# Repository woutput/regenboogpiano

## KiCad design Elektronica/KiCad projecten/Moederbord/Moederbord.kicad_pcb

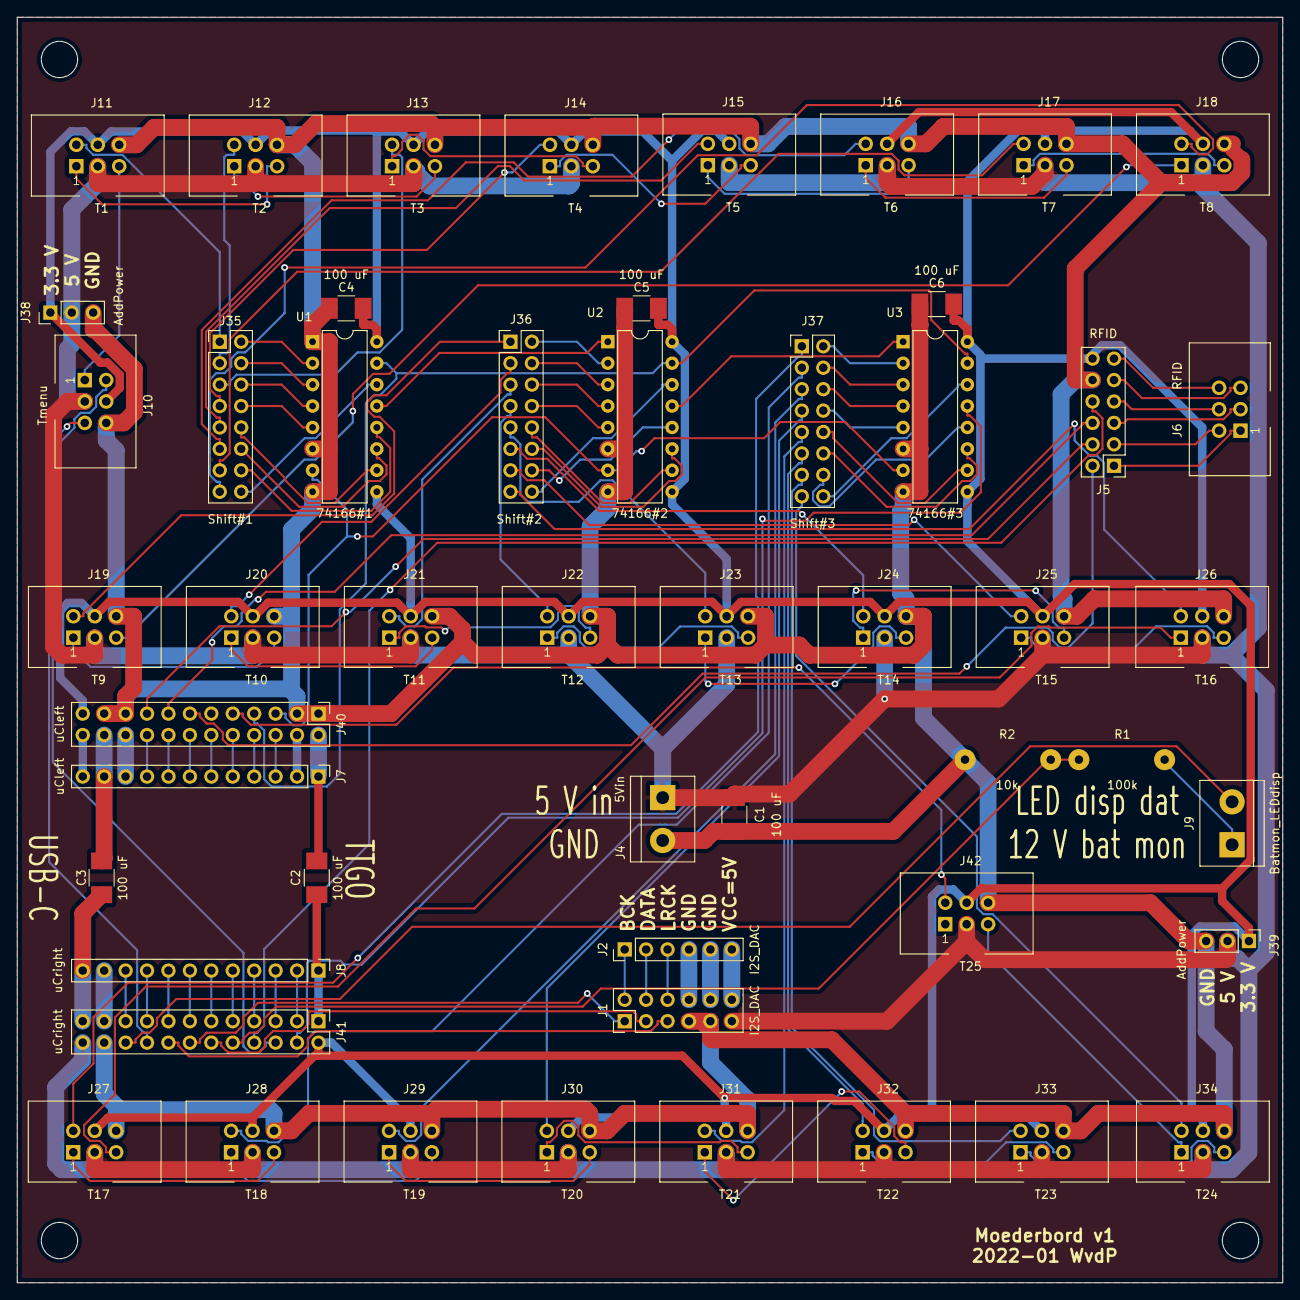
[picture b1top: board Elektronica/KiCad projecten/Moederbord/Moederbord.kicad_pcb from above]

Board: 2 copper layers, 150.0 x 150.0 mm, 56 parts (0 on the bottom side), 130 nets.

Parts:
C1, C2, C3, C4, C5, C6: 100 uF; C_1210_HandSoldering
J1: I2S_DAC; Pin_Header_Straight_2x06_Pitch2.54mm
J2: I2S_DAC; Socket_Strip_Straight_1x06_Pitch2.54mm
J4: 5Vin; TerminalBlock_2_P5.08mm
J5: RFID; Pin_Header_Straight_2x06_Pitch2.54mm
J6: RFID; IDC_Header_Straight_6pins
J7: uCleft; Socket_Strip_Straight_1x12_Pitch2.54mm
J8: uCright; Socket_Strip_Straight_1x12_Pitch2.54mm
J9: Batmon_LEDdisp; TerminalBlock_2_P5.08mm
J10: Tmenu; IDC_Header_Straight_6pins
J11: T1; IDC_Header_Straight_6pins
J12: T2; IDC_Header_Straight_6pins
J13: T3; IDC_Header_Straight_6pins
J14: T4; IDC_Header_Straight_6pins
J15: T5; IDC_Header_Straight_6pins
J16: T6; IDC_Header_Straight_6pins
J17: T7; IDC_Header_Straight_6pins
J18: T8; IDC_Header_Straight_6pins
J19: T9; IDC_Header_Straight_6pins
J20: T10; IDC_Header_Straight_6pins
J21: T11; IDC_Header_Straight_6pins
J22: T12; IDC_Header_Straight_6pins
J23: T13; IDC_Header_Straight_6pins
J24: T14; IDC_Header_Straight_6pins
J25: T15; IDC_Header_Straight_6pins
J26: T16; IDC_Header_Straight_6pins
J27: T17; IDC_Header_Straight_6pins
J28: T18; IDC_Header_Straight_6pins
J29: T19; IDC_Header_Straight_6pins
J30: T20; IDC_Header_Straight_6pins
J31: T21; IDC_Header_Straight_6pins
J32: T22; IDC_Header_Straight_6pins
J33: T23; IDC_Header_Straight_6pins
J34: T24; IDC_Header_Straight_6pins
J35: Shift#1; Pin_Header_Straight_2x08_Pitch2.54mm
J36: Shift#2; Pin_Header_Straight_2x08_Pitch2.54mm
J37: Shift#3; Pin_Header_Straight_2x08_Pitch2.54mm
J38, J39: AddPower; Pin_Header_Straight_1x03_Pitch2.54mm
J40: uCleft; Pin_Header_Straight_2x12_Pitch2.54mm
J41: uCright; Pin_Header_Straight_2x12_Pitch2.54mm
J42: T25; IDC_Header_Straight_6pins
R1: 100k; WireConnection_1.00mmDrill
R2: 10k; WireConnection_1.00mmDrill
U1: 74166#1; DIP-16_W7.62mm
U2: 74166#2; DIP-16_W7.62mm
U3: 74166#3; DIP-16_W7.62mm
X1, X2, X3, X4: MountingHole_4.3mm_M4

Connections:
+3V3: C4.1, C5.1, C6.1, J5.12, J10.4, J11.4, J12.4, J13.4, J14.4, J15.4, J16.4, J17.4, J18.4, J19.4, J20.4, J21.4, J22.4, J23.4, J24.4, J25.4, J26.4, J27.4, J28.4, J29.4, J30.4, J31.4, J32.4, J33.4, J34.4, J38.1, J39.1, J40.23, J41.2, J42.4, U1.9, U1.16, U2.9, U2.16, U3.9, U3.16
+5V: C1.2, J1.11, J4.1, J10.3, J11.3, J12.3, J13.3, J14.3, J15.3, J16.3, J17.3, J18.3, J19.3, J20.3, J21.3, J22.3, J23.3, J24.3, J25.3, J26.3, J27.3, J28.3, J29.3, J30.3, J31.3, J32.3, J33.3, J34.3, J38.2, J39.2, J41.24, J42.3
/Shift registers/T1: J35.2, U1.2
/Shift registers/T2: J35.4, U1.3
/Shift registers/T3: J35.6, U1.4
/Shift registers/T4: J35.8, U1.5
/Shift registers/T5: J35.10, U1.10
/Shift registers/T6: J35.12, U1.11
/Shift registers/T7: J35.14, U1.12
/Shift registers/T8: J35.16, U1.14
/Shift registers/T9: J36.2, U2.2
/Shift registers/T10: J36.4, U2.3
/Shift registers/T11: J36.6, U2.4
/Shift registers/T12: J36.8, U2.5
/Shift registers/T13: J36.10, U2.10
/Shift registers/T14: J36.12, U2.11
/Shift registers/T15: J36.14, U2.12
/Shift registers/T16: J36.16, U2.14
/Shift registers/T17: J37.2, U3.2
/Shift registers/T18: J37.4, U3.3
/Shift registers/T19: J37.6, U3.4
/Shift registers/T20: J37.8, U3.5
/Shift registers/T21: J37.10, U3.10
/Shift registers/T22: J37.12, U3.11
/Shift registers/T23: J37.14, U3.12
/Shift registers/T24: J37.16, U3.14
/Shift registers/s1_s2: U1.13, U2.1
/Shift registers/s2_s3: U2.13, U3.1
/Toetsmodules/LED1_LED2: J11.1, J12.5
/Toetsmodules/LED2_LED3: J12.1, J13.5
/Toetsmodules/LED3_LED4: J13.1, J14.5
/Toetsmodules/LED4_LED5: J14.1, J15.5
/Toetsmodules/LED5_LED6: J15.1, J16.5
/Toetsmodules/LED6_LED7: J16.1, J17.5
/Toetsmodules/LED7_LED8: J17.1, J18.5
/Toetsmodules/LED8_LED9: J18.1, J19.5
/Toetsmodules/LED9_LED10: J19.1, J20.5
/Toetsmodules/LED10_LED11: J20.1, J21.5
/Toetsmodules/LED11_LED12: J21.1, J22.5
/Toetsmodules/LED12_LED13: J22.1, J23.5
/Toetsmodules/LED13_LED14: J23.1, J24.5
/Toetsmodules/LED14_LED15: J24.1, J25.5
/Toetsmodules/LED15_LED16: J25.1, J26.5
/Toetsmodules/LED16_LED17: J26.1, J27.5
/Toetsmodules/LED17_LED18: J27.1, J28.5
/Toetsmodules/LED18_LED19: J28.1, J29.5
/Toetsmodules/LED19_LED20: J29.1, J30.5
/Toetsmodules/LED20_LED21: J30.1, J31.5
/Toetsmodules/LED21_LED22: J31.1, J32.5
/Toetsmodules/LED22_LED23: J32.1, J33.5
/Toetsmodules/LED23_LED24: J33.1, J34.5
/Toetsmodules/LED24_LED25: J34.1, J42.5
/Toetsmodules/LEDm_LED1: J10.1, J11.5
/Vbat12V: J9.1, R1.1
BatMon: J41.10, R1.2, R2.1
DAC_BCK: J1.1, J41.14
DAC_DATA: J1.3, J41.12
DAC_LRCK: J1.5, J41.16
GND: C1.1, C4.2, C5.2, C6.2, J1.7, J1.9, J4.2, J5.10, J10.6, J11.6, J12.6, J13.6, J14.6, J15.6, J16.6, J17.6, J18.6, J19.6, J20.6, J21.6, J22.6, J23.6, J24.6, J25.6, J26.6, J27.6, J28.6, J29.6, J30.6, J31.6, J32.6, J33.6, J34.6, J38.3, J39.3, J40.1, J40.3, J40.19, J40.21, J41.22, J42.6, R2.2, U1.1, U1.6, U1.8, U2.6, U2.8, U3.6, U3.8
LED_display_data: J9.2, J41.20
LED_rings_data: J10.5, J41.18
unnamed: C2.1, J8.1, J41.1
unnamed: C2.2, J7.1, J40.2
unnamed: C3.1, J8.12, J41.23
unnamed: C3.2, J7.11, J40.22
unnamed: J1.2, J2.1
unnamed: J1.4, J2.2
unnamed: J1.6, J2.3
unnamed: J1.8, J2.4
unnamed: J1.10, J2.5
unnamed: J1.12, J2.6
unnamed: J5.1, J6.1
unnamed: J5.3, J6.2
unnamed: J5.5, J6.3
unnamed: J5.7, J6.4
unnamed: J5.9, J6.5
unnamed: J5.11, J6.6
unnamed: J7.2, J40.4
unnamed: J7.3, J40.6
unnamed: J7.4, J40.8
unnamed: J7.5, J40.10
unnamed: J7.6, J40.12
unnamed: J7.7, J40.14
unnamed: J7.8, J40.16
unnamed: J7.9, J40.18
unnamed: J7.10, J40.20
unnamed: J7.12, J40.24
unnamed: J8.2, J41.3
unnamed: J8.3, J41.5
unnamed: J8.4, J41.7
unnamed: J8.5, J41.9
unnamed: J8.6, J41.11
unnamed: J8.7, J41.13
unnamed: J8.8, J41.15
unnamed: J8.9, J41.17
unnamed: J8.10, J41.19
unnamed: J8.11, J41.21
RFID_CS: J5.2, J40.13
RFID_MISO: J5.8, J41.8
RFID_MOSI: J5.6, J40.15
RFID_SCLK: J5.4, J40.17
Shift_CLK: J40.5, U1.7, U2.7, U3.7
Shift_SH_LDn: J40.7, U1.15, U2.15, U3.15
Shift_data: J41.4, U3.13
Touch1: J11.2, J35.1
Touch2: J12.2, J35.3
Touch3: J13.2, J35.5
Touch4: J14.2, J35.7
Touch5: J15.2, J35.9
Touch6: J16.2, J35.11
Touch7: J17.2, J35.13
Touch8: J18.2, J35.15
Touch9: J19.2, J36.1
Touch10: J20.2, J36.3
Touch11: J21.2, J36.5
Touch12: J22.2, J36.7
Touch13: J23.2, J36.9
Touch14: J24.2, J36.11
Touch15: J25.2, J36.13
Touch16: J26.2, J36.15
Touch17: J27.2, J37.1
Touch18: J28.2, J37.3
Touch19: J29.2, J37.5
Touch20: J30.2, J37.7
Touch21: J31.2, J37.9
Touch22: J32.2, J37.11
Touch23: J33.2, J37.13
Touch24: J34.2, J37.15
Touch25: J40.9, J42.2
Touch_menu: J10.2, J41.6

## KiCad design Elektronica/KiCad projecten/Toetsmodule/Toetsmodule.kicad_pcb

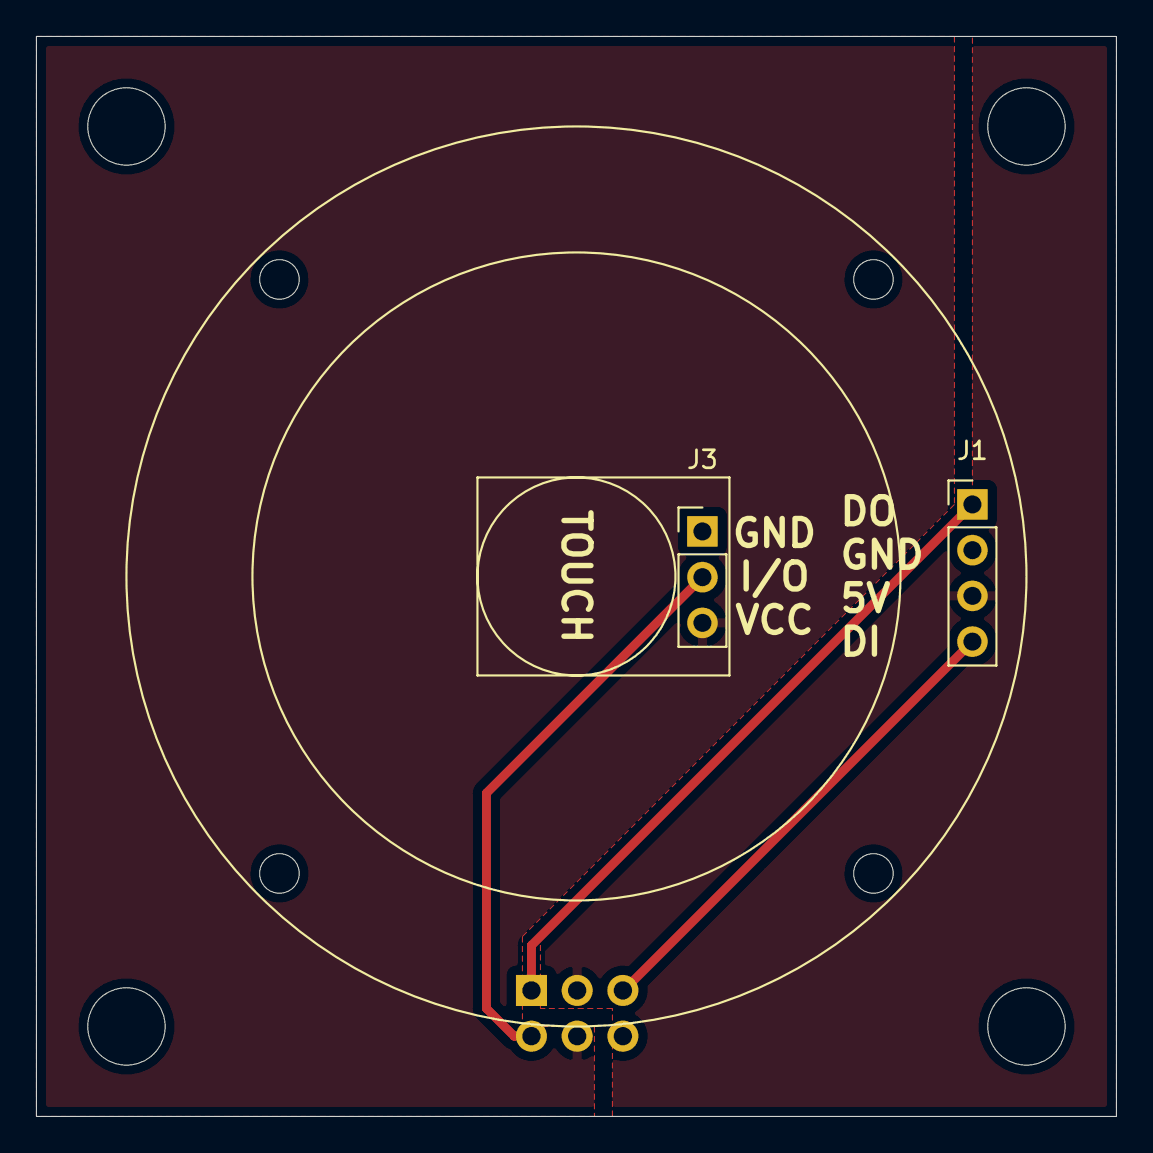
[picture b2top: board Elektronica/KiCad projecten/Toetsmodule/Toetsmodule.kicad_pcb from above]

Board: 2 copper layers, 60.0 x 60.0 mm, 3 parts (1 on the bottom side), 6 nets.

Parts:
J1: Conn_01x04_Male; Pin_Header_Straight_1x04_Pitch2.54mm
J2: Conn_01x06_Male; IDC_Header_Straight_6pins
J3: Touch module; Pin_Header_Straight_1x03_Pitch2.54mm

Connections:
+3V3: J2.4, J3.3
+5V: J1.3, J2.3
/LED_in: J1.4, J2.5
/LED_out: J1.1, J2.1
/Touch_output: J2.2, J3.2
GND: J1.2, J2.6, J3.1

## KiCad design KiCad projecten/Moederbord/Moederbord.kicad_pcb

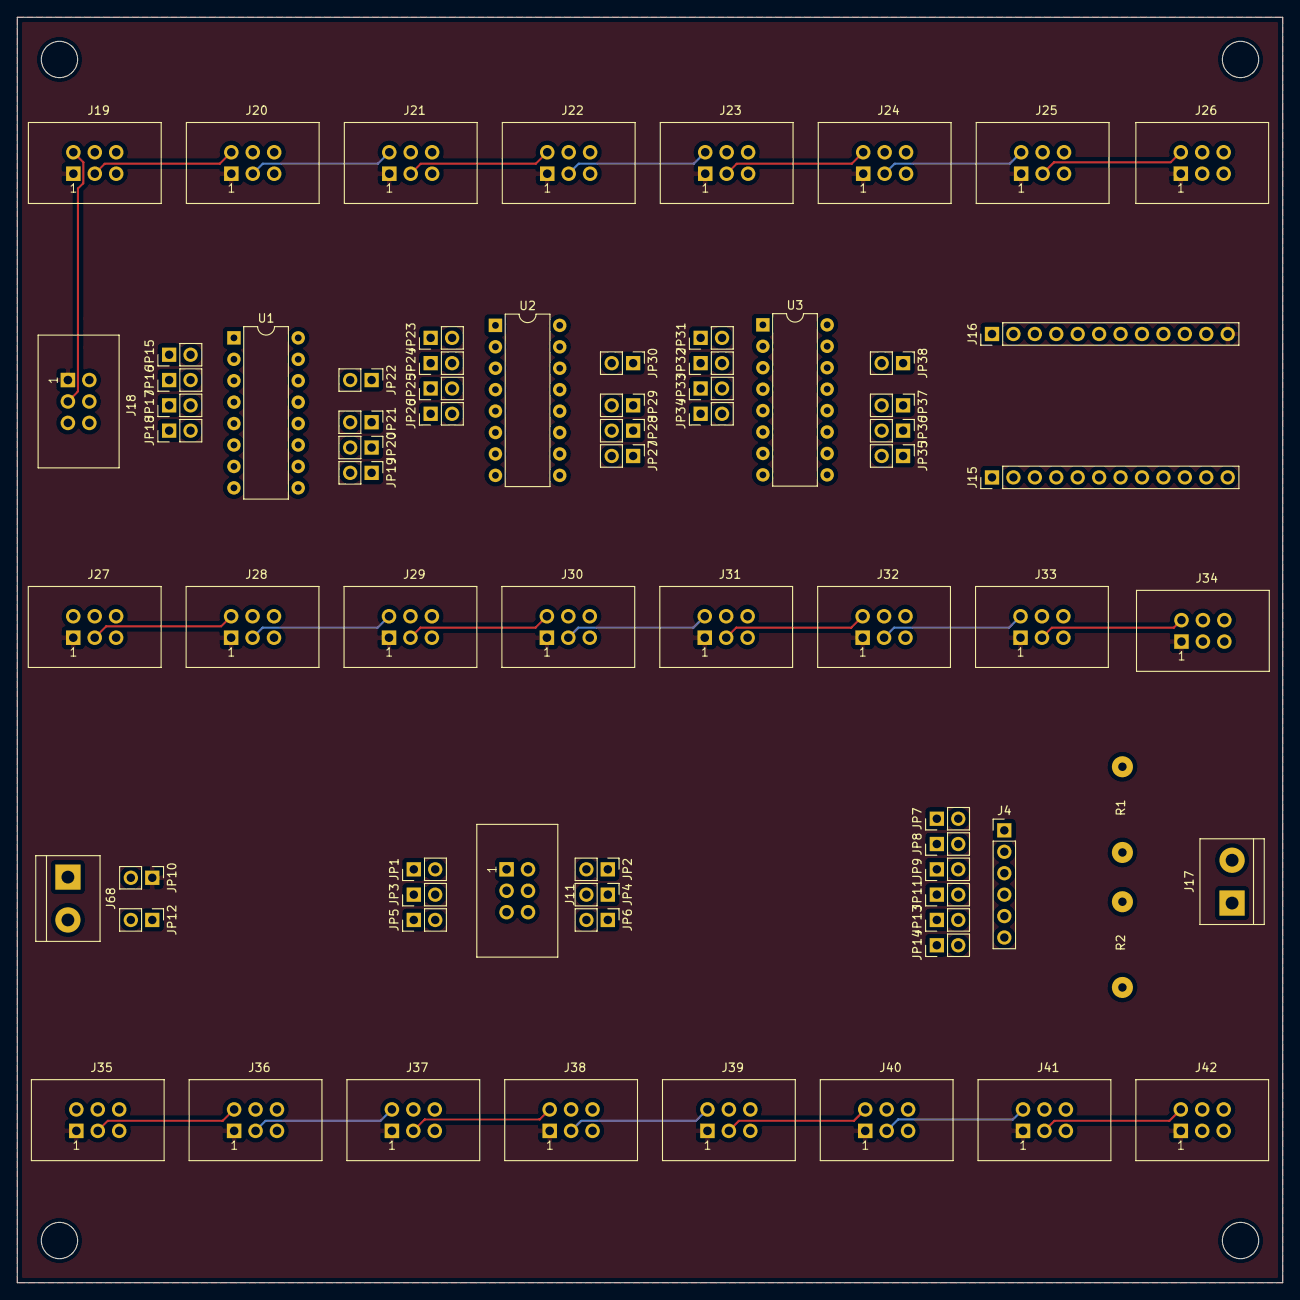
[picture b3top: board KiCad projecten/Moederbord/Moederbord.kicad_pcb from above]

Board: 2 copper layers, 150.0 x 150.0 mm, 74 parts (0 on the bottom side), 108 nets.

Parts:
J4: I2S_DAC; Socket_Strip_Straight_1x06_Pitch2.54mm
J11: Conn_01x06_Female; IDC_Header_Straight_6pins
J15, J16: Conn_01x12_Female; Socket_Strip_Straight_1x12_Pitch2.54mm
J17, J68: Screw_Terminal_01x02; TerminalBlock_2_P5.08mm
J18, J19, J20, J21, J22, J23, J24, J25, J26, J27, J28, J29, J30, J31, J32, J33, J34, J35, J36, J37, J38, J39, J40, J41, J42: Conn_01x06_Male; IDC_Header_Straight_6pins
JP1, JP2, JP3, JP4, JP5, JP6, JP7, JP8, JP9, JP10, JP11, JP12, JP13, JP14, JP15, JP16, JP17, JP18, JP19, JP20, JP21, JP22, JP23, JP24, JP25, JP26, JP27, JP28, JP29, JP30, JP31, JP32, JP33, JP34, JP35, JP36, JP37, JP38: Jumper; Jumper_1x2_Pitch2.54mm
R1: 10k; WireConnection_1.00mmDrill
R2: 2k7; WireConnection_1.00mmDrill
U1, U2, U3: 74166; DIP-16_W7.62mm

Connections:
+3V3: J15.12, J16.1, JP6.1, JP14.1, U1.9, U2.9, U3.9
+5V: J16.12, J18.1, J19.1, J20.1, J21.1, J22.1, J23.1, J24.1, J25.1, J26.1, J27.1, J28.1, J29.1, J30.1, J31.1, J32.1, J33.1, J34.1, J35.1, J36.1, J37.1, J38.1, J39.1, J40.1, J41.1, J42.1, JP10.1
BatMon: J16.5, R1.2, R2.1
DAC_BCK: J16.7, JP7.1
DAC_DATA: J16.6, JP8.1
DAC_LRCK: J16.8, JP9.1
GND: J15.1, J15.2, J15.10, J15.11, J16.11, J18.5, J19.5, J20.5, J21.5, J22.5, J23.5, J24.5, J25.5, J26.5, J27.5, J28.5, J29.5, J30.5, J31.5, J32.5, J33.5, J34.5, J35.5, J36.5, J37.5, J38.5, J39.5, J40.5, J41.5, J42.5, JP5.1, JP11.1, JP12.1, JP13.1, R2.2, U1.1, U1.6, U1.8, U2.6, U2.8, U3.6, U3.8
LED_rings_data: J16.9, J18.2
unnamed: J4.1, JP7.2
unnamed: J4.2, JP8.2
unnamed: J4.3, JP9.2
unnamed: J4.4, JP11.2
unnamed: J4.5, JP13.2
unnamed: J4.6, JP14.2
unnamed: J11.1, JP1.2
unnamed: J11.2, JP2.2
unnamed: J11.3, JP3.2
unnamed: J11.4, JP4.2
unnamed: J11.5, JP5.2
unnamed: J11.6, JP6.2
unnamed: J17.1, R1.1
unnamed: J18.3, J19.2
unnamed: J19.3, J20.2
unnamed: J20.3, J21.2
unnamed: J21.3, J22.2
unnamed: J22.3, J23.2
unnamed: J23.3, J24.2
unnamed: J24.3, J25.2
unnamed: J25.3, J26.2
unnamed: J26.3, J27.2
unnamed: J27.3, J28.2
unnamed: J28.3, J29.2
unnamed: J29.3, J30.2
unnamed: J30.3, J31.2
unnamed: J31.3, J32.2
unnamed: J32.3, J33.2
unnamed: J33.3, J34.2
unnamed: J34.3, J35.2
unnamed: J35.3, J36.2
unnamed: J36.3, J37.2
unnamed: J37.3, J38.2
unnamed: J38.3, J39.2
unnamed: J39.3, J40.2
unnamed: J40.3, J41.2
unnamed: J41.3, J42.2
unnamed: J68.1, JP10.2
unnamed: J68.2, JP12.2
unnamed: JP15.2, U1.2
unnamed: JP16.2, U1.3
unnamed: JP17.2, U1.4
unnamed: JP18.2, U1.5
unnamed: JP19.2, U1.10
unnamed: JP20.2, U1.11
unnamed: JP21.2, U1.12
unnamed: JP22.2, U1.14
unnamed: JP23.2, U2.2
unnamed: JP24.2, U2.3
unnamed: JP25.2, U2.4
unnamed: JP26.2, U2.5
unnamed: JP27.2, U2.10
unnamed: JP28.2, U2.11
unnamed: JP29.2, U2.12
unnamed: JP30.2, U2.14
unnamed: JP31.2, U3.2
unnamed: JP32.2, U3.3
unnamed: JP33.2, U3.4
unnamed: JP34.2, U3.5
unnamed: JP35.2, U3.10
unnamed: JP36.2, U3.11
unnamed: JP37.2, U3.12
unnamed: JP38.2, U3.14
unnamed: U1.13, U2.1
unnamed: U2.13, U3.1
RFID_CS: J15.7, JP1.1
RFID_MISO: J16.4, JP4.1
RFID_MOSI: J15.8, JP3.1
RFID_SCLK: J15.9, JP2.1
Shift_CLK: J15.3, U1.7, U2.7, U3.7
Shift_SH_LDn1: J15.4, U1.15
Shift_SH_LDn2: J15.5, U2.15
Shift_SH_LDn3: J15.6, U3.15
Shift_data: J16.2, U3.13
Touch1: J19.4, JP15.1
Touch2: J20.4, JP16.1
Touch3: J21.4, JP17.1
Touch4: J22.4, JP18.1
Touch5: J23.4, JP19.1
Touch6: J24.4, JP20.1
Touch7: J25.4, JP21.1
Touch8: J26.4, JP22.1
Touch9: J27.4, JP23.1
Touch10: J28.4, JP24.1
Touch11: J29.4, JP25.1
Touch12: J30.4, JP26.1
Touch13: J31.4, JP27.1
Touch14: J32.4, JP28.1
Touch15: J33.4, JP29.1
Touch16: J34.4, JP30.1
Touch17: J35.4, JP31.1
Touch18: J36.4, JP32.1
Touch19: J37.4, JP33.1
Touch20: J38.4, JP34.1
Touch21: J39.4, JP35.1
Touch22: J40.4, JP36.1
Touch23: J41.4, JP37.1
Touch24: J42.4, JP38.1
Touch_menu: J16.3, J18.4
VCC: U1.16, U2.16, U3.16

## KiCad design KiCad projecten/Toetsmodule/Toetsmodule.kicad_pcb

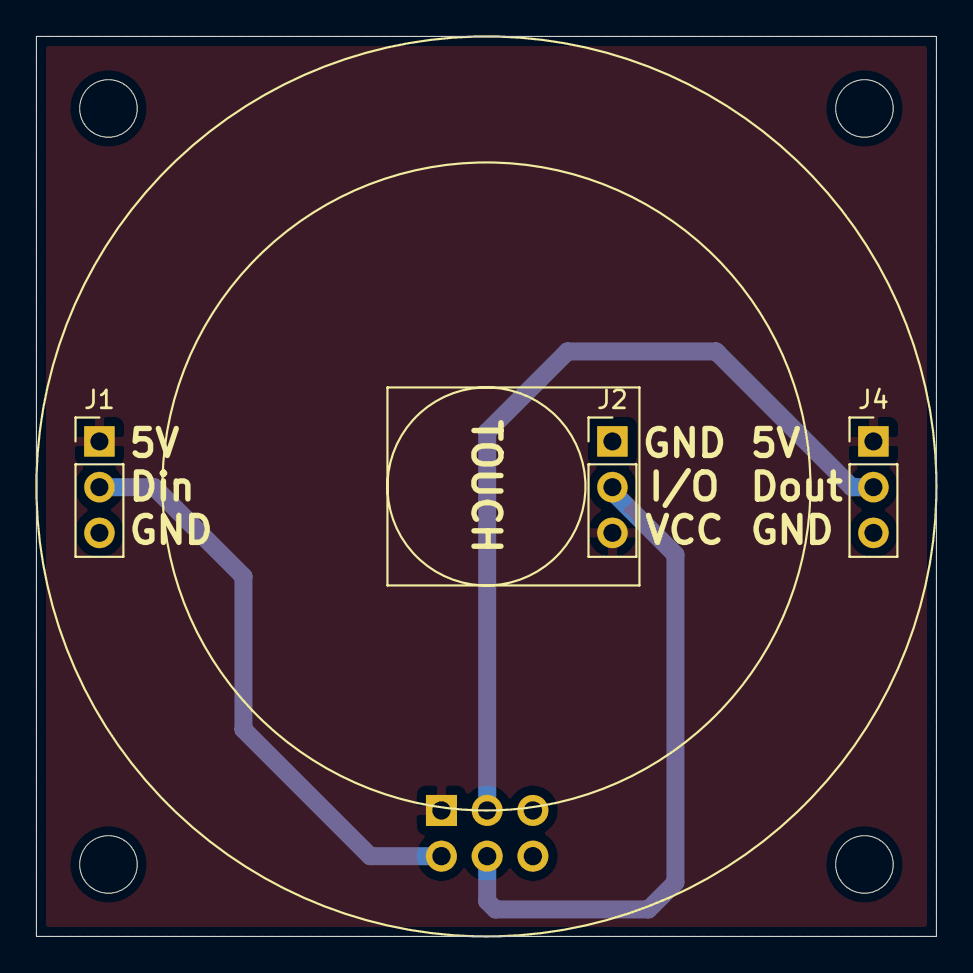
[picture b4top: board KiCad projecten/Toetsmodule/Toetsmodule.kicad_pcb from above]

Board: 2 copper layers, 50.0 x 50.0 mm, 4 parts (1 on the bottom side), 5 nets.

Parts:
J1, J4: Conn_01x03_Male; Pin_Header_Straight_1x03_Pitch2.54mm
J2: Touch module; Pin_Header_Straight_1x03_Pitch2.54mm
J3: Conn_01x06_Male; IDC_Header_Straight_6pins

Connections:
+5V: J1.1, J2.3, J3.1, J4.1
/LED_in: J1.2, J3.2
/LED_out: J3.3, J4.2
/Touch_output: J2.2, J3.4
GND: J1.3, J2.1, J3.5, J4.3

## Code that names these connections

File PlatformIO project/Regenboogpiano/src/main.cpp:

//// Important constants
#define LED_BRIGHTNESS 25 // 0...255
#define LED_DISPLAY_BRIGHTNESS LED_BRIGHTNESS // 0...255
#define LED_RINGS_BRIGHTNESS LED_BRIGHTNESS // 0...255

//// Pins
// DAC
#define PIN_DAC_DATA     32
#define PIN_DAC_BCLK     33
#define PIN_DAC_LRCLK    25

// TFT display (fixed, do not change)
#define PIN_TFT_CS         5
#define PIN_TFT_RST       -1
#define PIN_TFT_DC        16
#define PIN_TFT_BACKLIGHT  4
#define PIN_TFT_MOSI      19
#define PIN_TFT_SCLK      18

// LEDs
#define PIN_LED_RINGS   26
#define PIN_LED_DISPLAY 27

// RFID reader
#define PIN_RFID_RESET  UINT8_MAX // not connected
#define PIN_RFID_CS     15
#define PIN_RFID_SCK    12
#define PIN_RFID_MISO   38
#define PIN_RFID_MOSI   13

// Shift registers
#define PIN_SHIFT_CLK   21
#define PIN_SHIFT_SHLD1 22
#define PIN_SHIFT_SHLD2 17
#define PIN_SHIFT_SHLD3  2
#define PIN_SHIFT_DATA  36

// Test buttons on controller board
#define PIN_TEST_BUTTON_LEFT 0
#define PIN_TEST_BUTTON_RIGHT 35

//// Less important constants
// TODO: minimize this
// #define SHIFT_REGISTERS_SMALL_DELAY__MS 0
// TODO: change from 1 (test) to 3 (real)
#define NUMBER_OF_SHIFT_REGISTERS 1
#define NUMBER_OF_SHIFTS (NUMBER_OF_SHIFT_REGISTERS * 8)

// TODO: change from 1 (test) to 25 (real)
#define NUMBER_OF_LED_RINGS 1
#define NUMBER_OF_LEDS_PER_LED_RING 12

//// Include libraries
#include <Arduino.h>
#include <WiFi.h>
#include "AudioFileSourcePROGMEM.h"
#include "AudioGeneratorMP3.h"
#include "AudioOutputI2S.h"
#include <Adafruit_GFX.h>    // Core graphics library
#include <Adafruit_ST7789.h> // Hardware-specific library for ST7789
#include <SPI.h>
#include "FS.h"
#include "SD.h"
#include <Adafruit_NeoMatrix.h>
#include <Adafruit_NeoPixel.h>
#include <MFRC522.h>

#include "left.h"
#include "right.h"



// Audio
AudioGeneratorMP3 *mp3;
AudioFileSourcePROGMEM *file;
AudioOutputI2S *out;

// TFT display
SPIClass* spi = &SPI;
Adafruit_ST7789 tft = Adafruit_ST7789(PIN_TFT_CS, PIN_TFT_DC, PIN_TFT_MOSI, PIN_TFT_SCLK, PIN_TFT_RST); // TODO: remove last argument, because default is already -1

// LED display
Adafruit_NeoMatrix LED_display = Adafruit_NeoMatrix(32, 8, PIN_LED_DISPLAY,
  NEO_MATRIX_TOP     + NEO_MATRIX_LEFT +
  NEO_MATRIX_COLUMNS + NEO_MATRIX_ZIGZAG,
  NEO_GRB            + NEO_KHZ800);

// LED rings
Adafruit_NeoPixel LED_rings = Adafruit_NeoPixel(NUMBER_OF_LEDS_PER_LED_RING * NUMBER_OF_LED_RINGS, PIN_LED_RINGS, NEO_GRB + NEO_KHZ800);

// RFID reader
MFRC522 mfrc522(PIN_RFID_CS, PIN_RFID_RESET);  // Create MFRC522 instance

// Shift registers
int touch_sensor_state[NUMBER_OF_SHIFTS]; // TODO change to boolean when possible



//// Functions
void dump_byte_array(byte *buffer, byte bufferSize) {
  for (byte i = 0; i < bufferSize; i++) {
    Serial.print(buffer[i] < 0x10 ? " 0" : " ");
    Serial.print(buffer[i], HEX);
  }
}

void printDirectory(File dir, int numTabs) {
  while (true) {

    File entry =  dir.openNextFile();
    if (! entry) {
      // no more files
      break;
    }
    for (uint8_t i = 0; i < numTabs; i++) {
      Serial.print('\t');
    }
    Serial.print(entry.name());
    if (entry.isDirectory()) {
      Serial.println("/");
      printDirectory(entry, numTabs + 1);
    } else {
      // files have sizes, directories do not
      Serial.print("\t\t");
      Serial.println(entry.size(), DEC);
    }
    entry.close();
  }
}



//// Setup
void setup()
{
  // Debug to serial
  Serial.begin(115200);
	while (!Serial); // wait for serial port to connect. Needed for native USB port only
  Serial.println("Begin of setup");

  // WiFi
  WiFi.mode(WIFI_OFF); // TODO turn on WiFi later for firmware updates

  // Set pin modes
  // Test buttons
  pinMode(PIN_TEST_BUTTON_LEFT, INPUT_PULLUP);
  pinMode(PIN_TEST_BUTTON_RIGHT, INPUT_PULLUP);
  // Shift registers
  pinMode(PIN_SHIFT_CLK, OUTPUT);
  pinMode(PIN_SHIFT_SHLD1, OUTPUT);
  pinMode(PIN_SHIFT_SHLD2, OUTPUT);
  pinMode(PIN_SHIFT_SHLD3, OUTPUT);
  pinMode(PIN_SHIFT_DATA, INPUT);

  // // Audio
  // audioLogger = &Serial;
  // file = new AudioFileSourcePROGMEM(left_h, sizeof(left_h));
  // out = new AudioOutputI2S();
  // out->SetPinout(PIN_DAC_BCLK, PIN_DAC_LRCLK, PIN_DAC_DATA);
  // mp3 = new AudioGeneratorMP3();

  // TFT display
  tft.init(135, 240);
  tft.setRotation(1);
  pinMode(PIN_TFT_BACKLIGHT, OUTPUT);
  digitalWrite(PIN_TFT_BACKLIGHT, HIGH); // Backlight on

  // // LED display
  // LED_display.begin();
  // LED_display.setTextWrap(false);
  // LED_display.setBrightness(LED_DISPLAY_BRIGHTNESS);
  // LED_display.setTextColor(LED_display.Color(0, 0, 255));
  // LED_display.show(); // Initialize all pixels to 'off'

  // LED rings
  LED_rings.begin();
  LED_rings.setBrightness(LED_RINGS_BRIGHTNESS);
  LED_rings.show(); // Initialize all pixels to 'off'

  // // RFID reader
	// SPI.begin(PIN_RFID_SCK, PIN_RFID_MISO, PIN_RFID_MOSI, PIN_RFID_CS);
	// mfrc522.PCD_Init();
	// delay(4); // Optional delay. Some board do need more time after init to be ready, see Readme
  // mfrc522.PCD_SetAntennaGain(mfrc522.RxGain_max);

  Serial.println("End of setup");



  //// Debug/test only, TODO: remove this
  // // LED display
  // LED_display.fillScreen(0);
  // LED_display.setCursor(0, 0);
  // LED_display.print(F("Regenboogpiano"));
  // LED_display.show();
  // LED rings
  for(uint16_t i = 0; i < LED_rings.numPixels(); i++)
  {
    LED_rings.setPixelColor(i, i * 21);
  }
  LED_rings.show();
  // TFT display
  tft.fillScreen(ST77XX_BLACK);
  tft.setCursor(0, 0);
  tft.setTextSize(2);
  tft.setTextColor(ST77XX_RED);
  tft.print("R");
  tft.setTextColor(ST77XX_RED);
  tft.print("e");
  tft.setTextColor(ST77XX_ORANGE);
  tft.print("g");
  tft.setTextColor(ST77XX_ORANGE);
  tft.print("e");
  tft.setTextColor(ST77XX_YELLOW);
  tft.print("n");
  tft.setTextColor(ST77XX_YELLOW);
  tft.print("b");
  tft.setTextColor(ST77XX_GREEN);
  tft.print("o");
  tft.setTextColor(ST77XX_GREEN);
  tft.print("o");
  tft.setTextColor(ST77XX_CYAN);
  tft.print("g");
  tft.setTextColor(ST77XX_CYAN);
  tft.print("p");
  tft.setTextColor(ST77XX_BLUE);
  tft.print("i");
  tft.setTextColor(ST77XX_BLUE);
  tft.print("a");
  tft.setTextColor(ST77XX_MAGENTA);
  tft.print("n");
  tft.setTextColor(ST77XX_MAGENTA);
  tft.print("o");
  // // RFID reader
	// mfrc522.PCD_DumpVersionToSerial(); // Show details of PCD - MFRC522 Card Reader details
}

// LED ring rainbow demo
uint16_t step = 0;
bool already_done = false;

//// Loop
void loop()
{
  // // Audio
  // if (digitalRead(PIN_TEST_BUTTON_RIGHT) == LOW)
  // {
  //   if (mp3->isRunning())
  //     mp3->stop();
  //   file->open(right_h, sizeof(right_h));
  //   mp3->begin(file, out);
  // }

  // if (digitalRead(PIN_TEST_BUTTON_LEFT) == LOW)
  // {
  //   if (mp3->isRunning())
  //     mp3->stop();
  //   file->open(left_h, sizeof(left_h));
  //   mp3->begin(file, out);
  // }

  // if (mp3->isRunning())
  // {
  //   if (!mp3->loop()) mp3->stop();
  // }


  //   // RFID reader
  // if ((millis() % 100) == 0)
  // {
  //   if (mfrc522.PICC_IsNewCardPresent())
  //   {
  //     // Select one of the cards
  //     if (mfrc522.PICC_ReadCardSerial())
  //     {
  //       Serial.print(F("Card UID:"));
  //       // mfrc522.PICC_DumpToSerial(&(mfrc522.uid));
  //       dump_byte_array(mfrc522.uid.uidByte, mfrc522.uid.size);
  //       Serial.println(F(""));
  //       mfrc522.PICC_HaltA();
  //     }
  //   }
  // }


  // // Shift registers
  // // Load inputs to shift registers
  // digitalWrite(PIN_SHIFT_CLK, LOW);
  // // delay(SHIFT_REGISTERS_SMALL_DELAY__MS);
  // digitalWrite(PIN_SHIFT_SHLD1, LOW);
  // digitalWrite(PIN_SHIFT_SHLD2, LOW);
  // digitalWrite(PIN_SHIFT_SHLD3, LOW);
  // // delay(SHIFT_REGISTERS_SMALL_DELAY__MS);
  // digitalWrite(PIN_SHIFT_CLK, HIGH);
  // // delay(SHIFT_REGISTERS_SMALL_DELAY__MS);
  // digitalWrite(PIN_SHIFT_CLK, LOW);
  // digitalWrite(PIN_SHIFT_SHLD1, HIGH);
  // digitalWrite(PIN_SHIFT_SHLD2, HIGH);
  // digitalWrite(PIN_SHIFT_SHLD3, HIGH);
  // // delay(SHIFT_REGISTERS_SMALL_DELAY__MS);
  // // Now shift out data
  // for (uint8_t shifts = 0; shifts < NUMBER_OF_SHIFTS; shifts++)
  // {
  //   digitalWrite(PIN_SHIFT_CLK, HIGH);
  //   // delay(SHIFT_REGISTERS_SMALL_DELAY__MS);
  //   touch_sensor_state[shifts] = digitalRead(PIN_SHIFT_DATA);
  //   Serial.print(touch_sensor_state[shifts]);
  //   digitalWrite(PIN_SHIFT_CLK, LOW);
  //   // delay(SHIFT_REGISTERS_SMALL_DELAY__MS);
  // }
  // Serial.println("");

  // LED ring rainbow demo
  // if ((millis() % 10) == 0)
  // {
  //   if (already_done == false)
  //   {
      step = step + 10;
      // if (step == UINT16_MAX)
      // {
      //   step = 0;
      // }
      LED_rings.rainbow(step);
      LED_rings.show();
      already_done = true;
//     }
//   }
//   else
//   {
//     already_done = false;
//   }
}

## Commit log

2021-11-30 Eerste versie
2021-11-30 Dingen naar map oud
2021-11-30 Update Sketchup-model
2021-11-30 Update software + dierengeluiden
2021-11-30 Verplaatsen naar mappen
2021-11-30 Update 3D-model
2021-11-30 Update bestellingen
2021-12-01 Tijdelijke bestanden verwijderen + .gitignore
2021-12-01 Update overzicht elektrisch schema
2021-12-01 Add an RFID library for future use
2021-12-01 Update moederbord schema
2021-12-03 Update schema moederbord
2021-12-06 Tijdelijke Excel-files toevoegen aan .gitignore
2021-12-06 Eerste toewijzingen van controller-pinnen
2021-12-06 Geen testprogramma's; MP3s uit PROGMEM en display
2021-12-06 Added micro SD card support
2021-12-08 Update software en pin-toewijzingen
2021-12-08 Maak ketting van shift-registers
2021-12-08 Nieuwe MP3s van piano
2021-12-08 Definitie spellen
2021-12-09 Update na overleg
2021-12-10 Oud overleg verplaatsen
2021-12-10 Software update
2021-12-14 Update toetsmodule: 60 x 60 mm & M4 gaten
2021-12-14 microSD kaartlezer verwijderd; shift-registers in keten; 5e display verwijderd
2021-12-14 Update moederbord
2021-12-18 Update voor shift registers
2021-12-18 Bestanden ordenen in mappen
2021-12-19 Toetsmodule v1 klaar
2021-12-26 Datasheets + update moederbord
2021-12-28 Update software-diagram
2021-12-28 Update vanwege 25e toets (dus nu 26 toetsmodules met menu-knop)
2021-12-30 Schema's in PNG voor review
2022-01-02 Opzet structuur software
2022-01-05 Eerste versie van moederbord klaar
2022-01-07 Update software
2022-01-12 Klavier toegevoegd
2022-01-14 Update software diagram
2022-02-03 Kleurtjes
2022-02-06 Software update, now with MP3s from SPIFFS
2022-02-08 Nieuwe MP3s, nieuwe software en facturen
2022-03-08 Werkend beginpunt
2022-03-10 Nieuwe factuur en software update
2022-03-14 mp3 > roze
2022-03-18 update piano geluiden
2022-03-18 Revert "update piano geluiden"
    This reverts commit 9a3936e8f790cae8ba37aecb9c8e527b35c14cf3.
2022-03-18 update gitignore
2022-03-18 As in production on 2022-03-18
2025-02-08 Add OTA and blink
